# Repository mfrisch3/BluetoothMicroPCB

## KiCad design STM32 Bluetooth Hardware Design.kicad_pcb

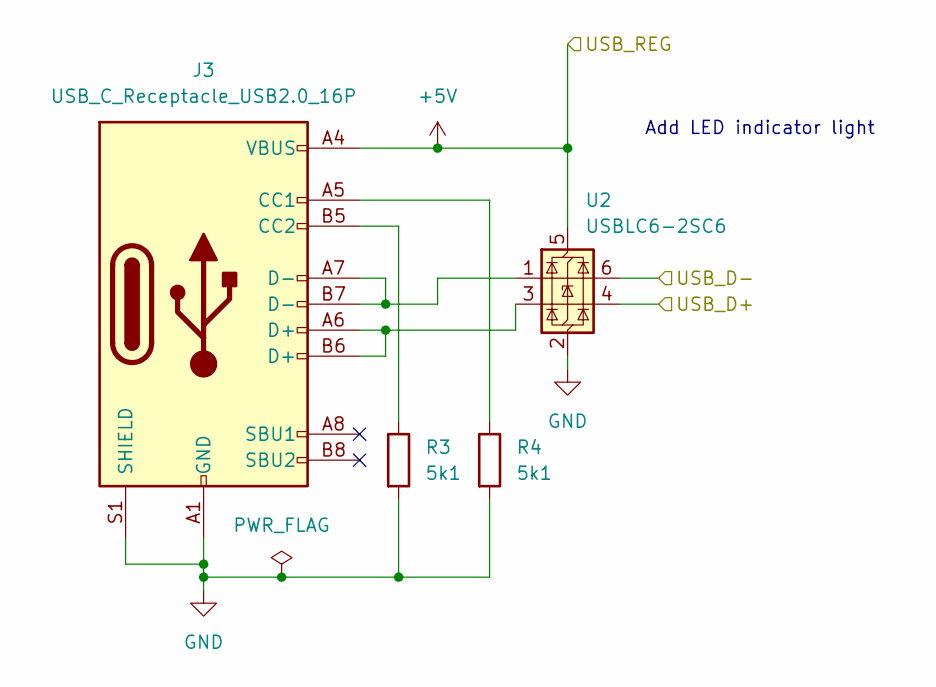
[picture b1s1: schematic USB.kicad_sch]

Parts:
J3: USB_C_Receptacle_USB2.0_16P; USB_C_Receptacle_GCT_USB4105-xx-A_16P_TopMnt_Horizontal
R3, R4: 5k1; R_0402_1005Metric
U2: USBLC6-2SC6; SOT-23-6

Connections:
+5V: J3.A4 (VBUS), J3.A9 (VBUS), J3.B4 (VBUS), J3.B9 (VBUS), U2.5 (VBUS); also elsewhere on the board
/MCU/USB_D+: U2.4 (I/O2); also elsewhere on the board
/MCU/USB_D-: U2.6 (I/O1); also elsewhere on the board
GND: J3.A1 (GND), J3.A12 (GND), J3.B1 (GND), J3.B12 (GND), J3.S1 (SHIELD), R3.2, R4.2, U2.2 (GND); also elsewhere on the board
unnamed: J3.A5 (CC1), R4.1
unnamed: J3.B5 (CC2), R3.1
unnamed: J3.A6 (D+), J3.B6 (D+), U2.3 (I/O2)
unnamed: J3.A7 (D-), J3.B7 (D-), U2.1 (I/O1)

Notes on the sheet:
Add LED indicator light

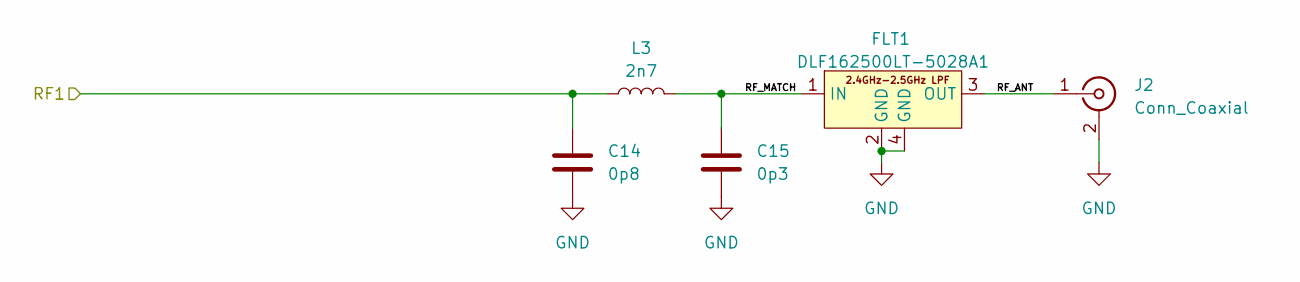
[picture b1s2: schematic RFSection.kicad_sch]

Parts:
C14: 0p8; C_0402_1005Metric
C15: 0p3; C_0402_1005Metric
FLT1: DLF162500LT-5028A1
J2: Conn_Coaxial; Molex_PicoBlade_53048-0410_1x04_P1.25mm_Horizontal
L3: 2n7; L_0402_1005Metric

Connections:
/MCU/RF1: C14.1, L3.1; also elsewhere on the board
/RF Section/RF_ANT: FLT1.3 (OUT), J2.1 (In)
/RF Section/RF_MATCH: C15.1, FLT1.1 (IN), L3.2
GND: C14.2, C15.2, FLT1.2 (GND), FLT1.4 (GND), J2.2 (Ext); also elsewhere on the board

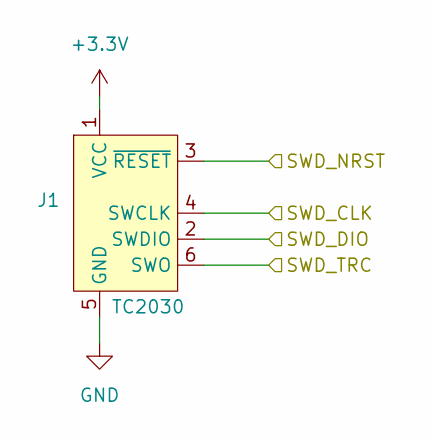
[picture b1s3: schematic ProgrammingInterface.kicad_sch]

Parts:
J1: TC2030; Tag-Connect_TC2030-IDC-FP_2x03_P1.27mm_Vertical

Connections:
+3.3V: J1.1 (VCC); also elsewhere on the board
/MCU/SWD_CLK: J1.4 (SWCLK); also elsewhere on the board
/MCU/SWD_DIO: J1.2 (SWDIO); also elsewhere on the board
/MCU/SWD_NRST: J1.3 (~RESET); also elsewhere on the board
/MCU/SWD_TRC: J1.6 (SWO); also elsewhere on the board
GND: J1.5 (GND); also elsewhere on the board

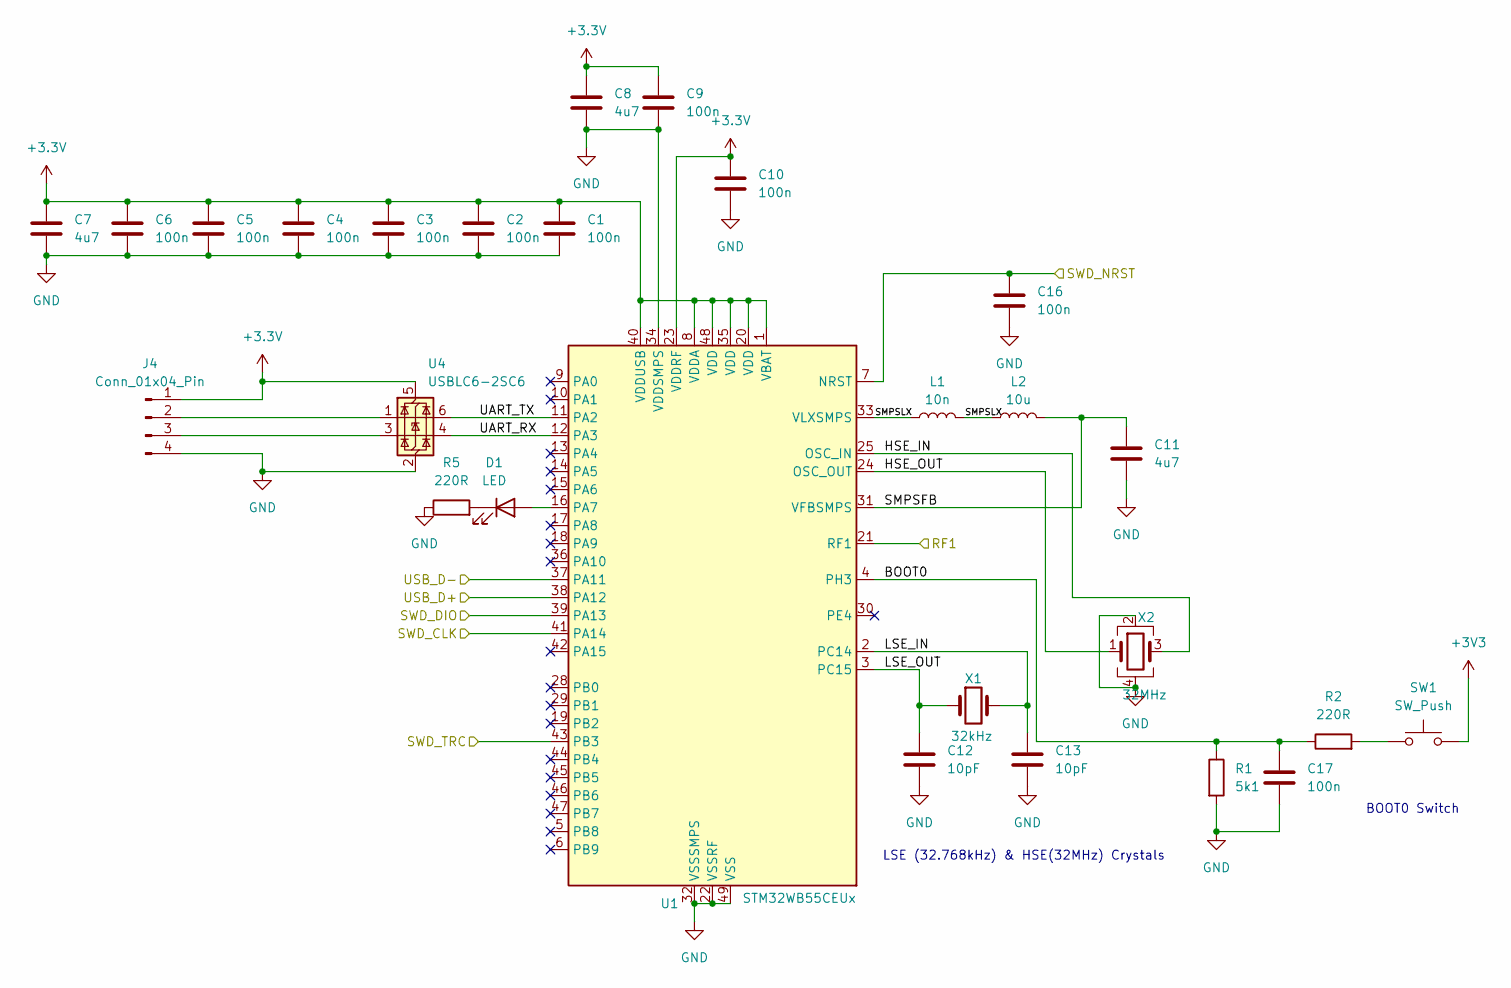
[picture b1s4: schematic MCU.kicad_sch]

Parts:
C1, C2, C3, C4, C5, C6, C9, C10, C16, C17: 100n; C_0402_1005Metric
C7, C8, C11: 4u7; C_0603_1608Metric
C12, C13: 10pF; C_0402_1005Metric
D1: LED; LED_0402_1005Metric
J4: Conn_01x04_Pin; U.FL_Hirose_U.FL-R-SMT-1_Vertical
L1: 10n; L_0402_1005Metric
L2: 10u; L_0805_2012Metric
R1: 5k1; R_0402_1005Metric
R2, R5: 220R; R_0402_1005Metric
SW1: SW_Push; SW_SPST_CK_RS282G05A3
U1: STM32WB55CEUx; QFN-48-1EP_7x7mm_P0.5mm_EP5.6x5.6mm
U4: USBLC6-2SC6; SOT-23-6
X1: 32kHz; Crystal_SMD_2012-2Pin_2.0x1.2mm
X2: 32MHz; Crystal_SMD_2016-4Pin_2.0x1.6mm

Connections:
+3.3V: C1.1, C2.1, C3.1, C4.1, C5.1, C6.1, C7.1, C8.1, C9.1, C10.1, J4.1, U1.1 (VBAT), U1.8 (VDDA), U1.20 (VDD), U1.23 (VDDRF), U1.35 (VDD), U1.40 (VDDUSB), U1.48 (VDD), U4.5 (VBUS); also elsewhere on the board
+3V3: SW1.2
/MCU/BOOT0: C17.1, R1.1, R2.1, U1.4 (PH3)
/MCU/HSE_IN: U1.25 (OSC_IN), X2.3
/MCU/HSE_OUT: U1.24 (OSC_OUT), X2.1
/MCU/LSE_IN: C13.1, U1.2 (PC14), X1.2
/MCU/LSE_OUT: C12.1, U1.3 (PC15), X1.1
/MCU/RF1: U1.21 (RF1); also elsewhere on the board
/MCU/SMPSFB: C11.1, L2.2, U1.31 (VFBSMPS)
/MCU/SMPSLX: L1.1, L1.2, L2.1, U1.33 (VLXSMPS)
/MCU/SWD_CLK: U1.41 (PA14); also elsewhere on the board
/MCU/SWD_DIO: U1.39 (PA13); also elsewhere on the board
/MCU/SWD_NRST: C16.1, U1.7 (NRST); also elsewhere on the board
/MCU/SWD_TRC: U1.43 (PB3); also elsewhere on the board
/MCU/UART_RX: U1.12 (PA3), U4.4 (I/O2)
/MCU/UART_TX: U1.11 (PA2), U4.6 (I/O1)
/MCU/USB_D+: U1.38 (PA12); also elsewhere on the board
/MCU/USB_D-: U1.37 (PA11); also elsewhere on the board
GND: C1.2, C2.2, C3.2, C4.2, C5.2, C6.2, C7.2, C8.2, C9.2, C10.2, C11.2, C12.2, C13.2, C16.2, C17.2, J4.4, R1.2, R5.1, U1.22 (VSSRF), U1.32 (VSSSMPS), U1.34 (VDDSMPS), U1.49 (VSS), U4.2 (GND), X2.2, X2.4; also elsewhere on the board
unnamed: D1.2 (A), U1.16 (PA7)
unnamed: D1.1 (K), R5.2
unnamed: J4.2, U4.1 (I/O1)
unnamed: J4.3, U4.3 (I/O2)
unnamed: R2.2, SW1.1

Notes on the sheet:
BOOT0 Switch
LSE (32.768kHz) & HSE(32MHz) Crystals

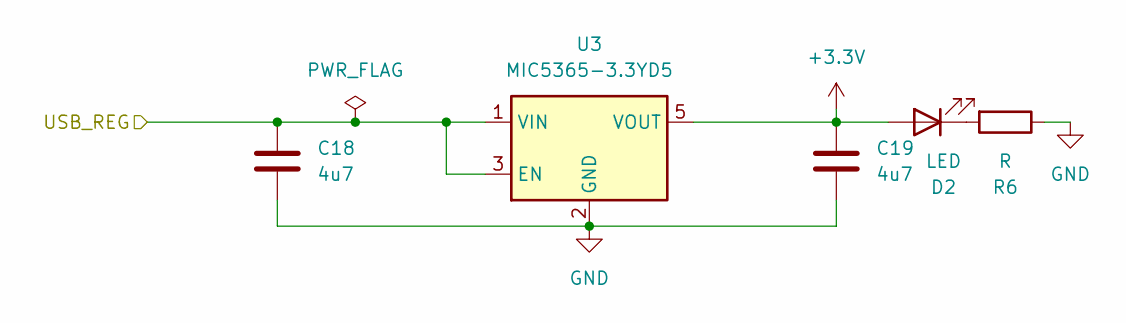
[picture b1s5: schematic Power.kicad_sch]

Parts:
C18, C19: 4u7; C_0603_1608Metric
D2: LED; LED_0402_1005Metric
R6: R; R_0402_1005Metric
U3: MIC5365-3.3YD5; SOT-23-5

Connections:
+3.3V: C19.1, D2.2 (A), U3.5 (VOUT); also elsewhere on the board
+5V: C18.1, U3.1 (VIN), U3.3 (EN); also elsewhere on the board
GND: C18.2, C19.2, R6.1, U3.2 (GND); also elsewhere on the board
unnamed: D2.1 (K), R6.2

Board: 4 copper layers, 42 parts (0 on the bottom side), 30 nets, no tracks yet.

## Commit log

2025-06-10 added crystals
2025-06-13 added schematic sections and stm32cube file
2025-06-20 finished rf section, added usb, and power sections
2025-07-30 fixed some nets
2025-07-30 fixed drc error
2025-08-08 added stuff
